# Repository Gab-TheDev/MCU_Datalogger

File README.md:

# MCU_Datalogger
**PCB design of an MCU datalogger**

This project is based on the Data Logger design from KiCad Like a Pro. It involves creating a printed circuit board (PCB) for a microcontroller-based system that records environmental data. The main goal is to design, simulate, and lay out a functional PCB using KiCad, while learning key concepts in schematic capture, component placement, routing, and generating manufacturing files.

The data logger includes a microcontroller, voltage regulation, sensor interfaces (like temperature or humidity sensors), and a method for storing or transmitting data, such as an SD card or serial output. The focus is on building a solid foundation in PCB design practices, including signal integrity, component footprints, and creating a professional-quality layout.

By completing this project, I aim to:
- Gain hands-on experience with KiCad’s schematic and PCB layout tools
- Understand the full workflow from schematic to fabrication
- Apply real-world design constraints (power supply, connectors, etc.)
- Build confidence in creating and testing custom electronics

**COMPONENT DESCRIPTION – ATmega328P based Data Logger**

**ATmega328P-A**<br>
Role: Main microcontroller unit (MCU).<br>
Function: Handles all logic and processing for the data logger. Responsible for reading sensors, managing storage (EEPROM), communicating with the RTC, and executing firmware routines.<br>
Interfaces: Supports I2C, UART, ISCP for embedded systems and data logging.<br>
Clock Input: Works with external crystals (16MHz) for stable timing.<br>

**DS1337S – Real-Time Clock (RTC) – SOIC-8**<br>
Role: Timekeeping chip for timestamping logged data.<br>
Function: Maintains calendar and clock time in the absence of MCU power. Communicates with the MCU over I2C.<br>
Features:
- Battery backup support (via V_BAT)
- 2x programmable square-wave/alarm outputs
- ±2ppm accuracy (with proper crystal)
- Package: SOIC-8 (SOIC127P600X175-8N)

**Battery Connector – PinHeader_1x02_P2.54mm_Vertical**<br>
Role: Backup power source connection for the RTC.<br>
Function: Connects a coin cell battery (e.g., CR2032) to the DS1337’s V_BAT pin to keep time when the main power is off.<br>
Package: Standard 2.54mm pitch, vertical pin header — allows easy external battery hookup or socket.<br>

**32.768 kHz Crystal – SMD_5032 (2-Pin)**<br>
Role: Real-Time Clock (RTC) timebase.<br>
Function: Provides a low-frequency clock source for the DS1337 RTC module to maintain accurate timekeeping with minimal power consumption.<br>
Typical Use: Used for generating 1-second ticks or sub-second timing in RTC chips.<br>
Package: SMD 5.0 x 3.2 mm, hand-solderable.<br>

**32.768 kHz Crystal – SMD_5032 (2-Pin)**<br>
Role: Real-Time Clock (RTC) timebase.<br>
Function: Provides a low-frequency clock source for the DS1337 RTC module to maintain accurate timekeeping with minimal power consumption.<br>
Typical Use: Used for generating 1-second ticks or sub-second timing in RTC chips.<br>
Package: SMD 5.0 x 3.2 mm, hand-solderable footprint.<br>

**24LC1025 – 128 Kbits I²C EEPROM (SOIC-8 Package)**<br>
Role: Non-volatile EEPROM used for persistent data storage in embedded systems. It ensures data retention even when powered off, making it ideal for data logging, configuration storage, and device identification.<br>
Function: It communicates via the I2C protocol and provides 128 Kbits of storage. Data can be written and read by the microcontroller, with the memory content preserved during power loss.<br>
Package: SOIC-8 5.3 x 5.3 mm with a pin pitch of 1.27 mm<br>

**CONCLUSION:**<br>
The MCU Data Logger project is a complete end-to-end solution for building an embedded system that can collect, process, and store data for later analysis. By utilizing KiCad for designing the schematic and PCB, this project serves as both a practical tool and a learning experience for those interested in embedded systems, sensor interfacing, and PCB design.

This repository aims to serve as a valuable resource for developers and hobbyists looking to create reliable and efficient data logging systems, contributing to the growing community of open-source embedded system designs.

## License
This project is licensed under the MIT License - see the LICENSE file for details

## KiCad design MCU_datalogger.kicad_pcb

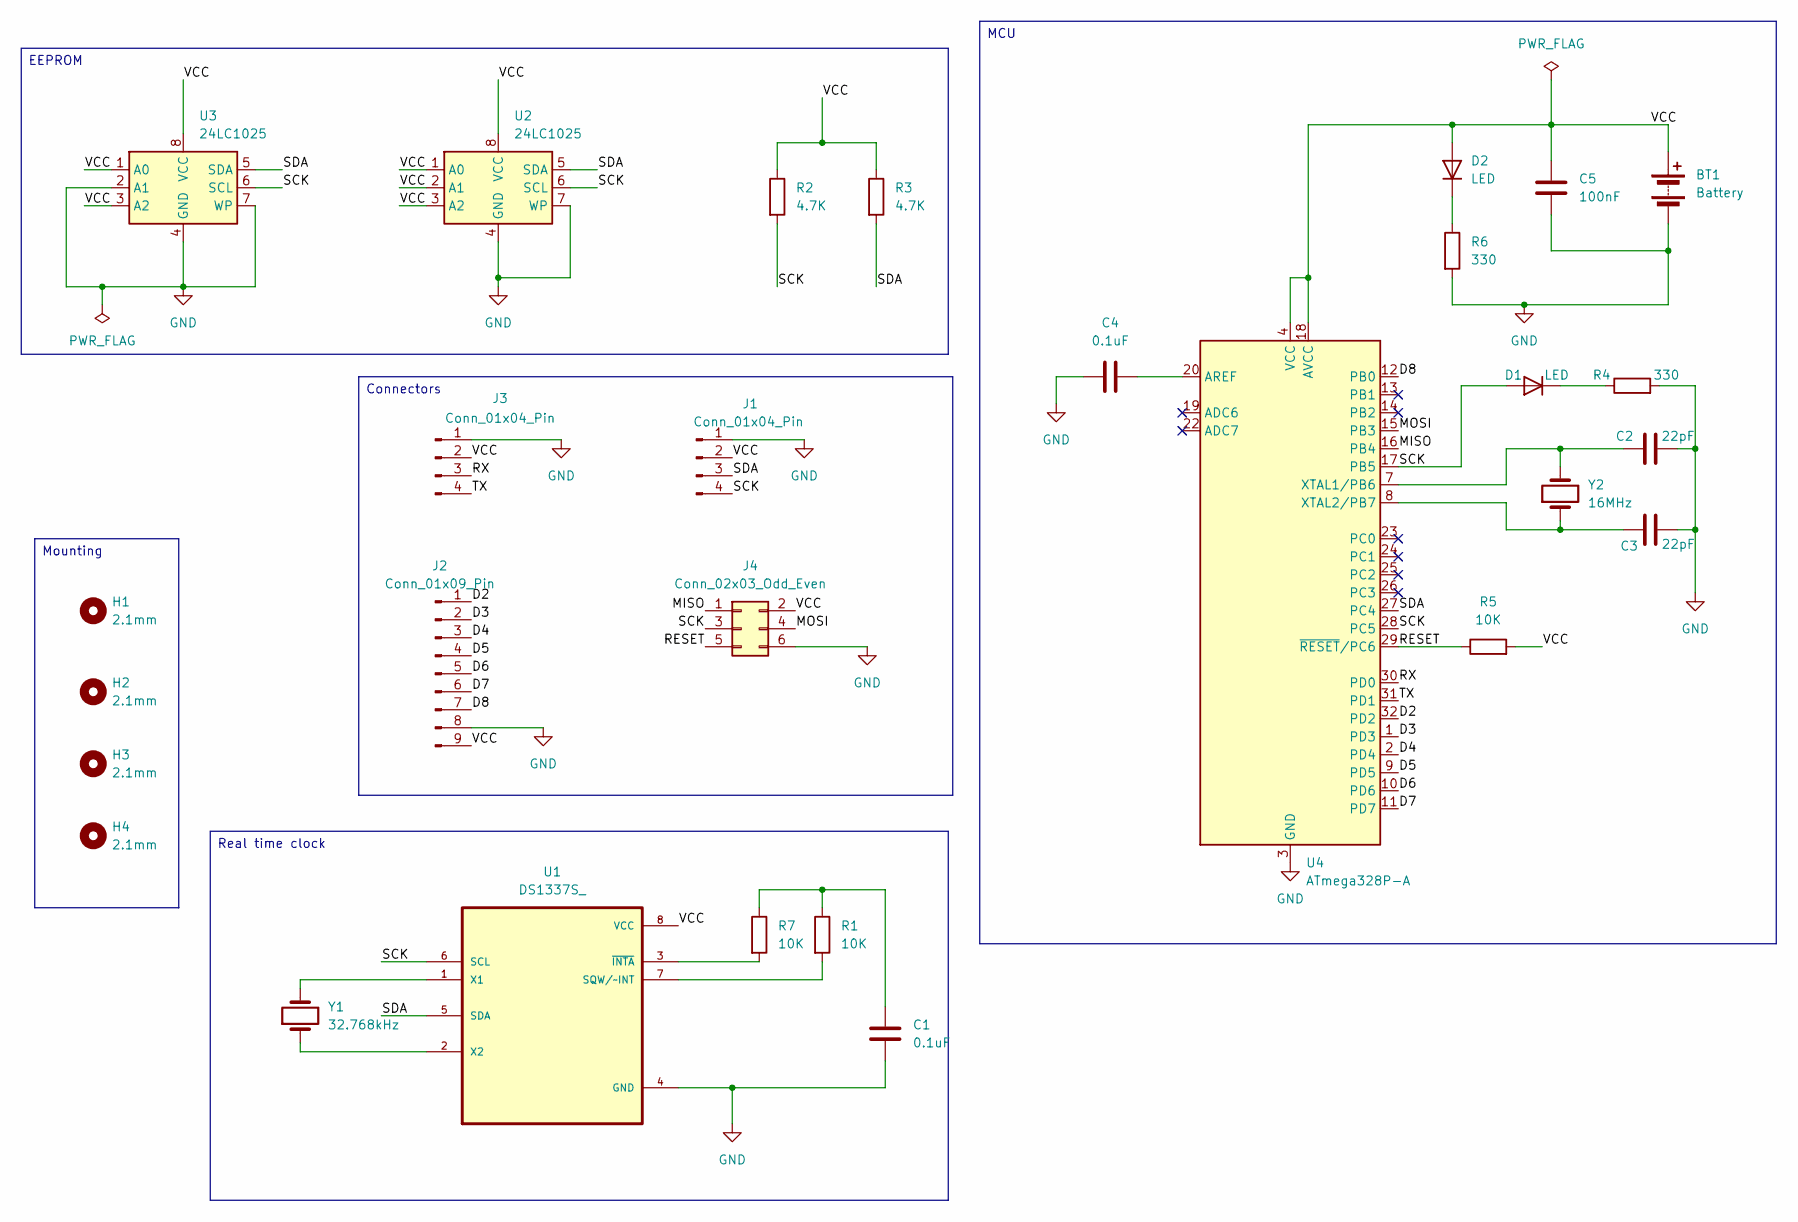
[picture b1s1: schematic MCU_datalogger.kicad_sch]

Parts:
BT1: Battery; PinHeader_1x02_P2.54mm_Vertical
C1, C4: 0.1uF; C_0805_2012Metric
C2, C3: 22pF; C_0805_2012Metric
C5: 100nF; C_0805_2012Metric
D1, D2: LED; LED_0805_2012Metric
H1, H2, H3, H4: 2.1mm; MountingHole_2.1mm
J1, J3: Conn_01x04_Pin; PinHeader_1x04_P2.54mm_Vertical
J2: Conn_01x09_Pin; PinHeader_1x09_P2.54mm_Vertical
J4: Conn_02x03_Odd_Even; PinHeader_2x03_P2.54mm_Vertical
R1, R5, R7: 10K; R_0805_2012Metric
R2, R3: 4.7K; R_0805_2012Metric
R4, R6: 330; R_0805_2012Metric
U1: DS1337S_; SOIC127P600X175-8N
U2, U3: 24LC1025; SOIC-8_5.3x5.3mm_P1.27mm
U4: ATmega328P-A; TQFP-32_7x7mm_P0.8mm
Y1: 32.768kHz; Crystal_SMD_5032-2Pin_5.0x3.2mm_HandSoldering
Y2: 16MHz; Crystal_SMD_5032-2Pin_5.0x3.2mm_HandSoldering

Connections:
/D2: J2.1, U4.32 (PD2)
/D3: J2.2, U4.1 (PD3)
/D4: J2.3, U4.2 (PD4)
/D5: J2.4, U4.9 (PD5)
/D6: J2.5, U4.10 (PD6)
/D7: J2.6, U4.11 (PD7)
/D8: J2.7, U4.12 (PB0)
/MISO: J4.1, U4.16 (PB4)
/MOSI: J4.4, U4.15 (PB3)
/RESET: J4.5, R5.1, U4.29 (~RESET/PC6)
/RX: J3.3, U4.30 (PD0)
/SCK: D1.2 (A), J1.4, J4.3, R2.2, U1.6 (SCL), U2.6 (SCL), U3.6 (SCL), U4.17 (PB5), U4.28 (PC5)
/SDA: J1.3, R3.2, U1.5 (SDA), U2.5 (SDA), U3.5 (SDA), U4.27 (PC4)
/TX: J3.4, U4.31 (PD1)
/VCC: BT1.1 (+), C5.1, D2.2 (A), J1.2, J2.9, J3.2, J4.2, R2.1, R3.1, R5.2, U1.8 (VCC), U2.1 (A0), U2.2 (A1), U2.3 (A2), U2.8 (VCC), U3.1 (A0), U3.3 (A2), U3.8 (VCC), U4.4 (VCC), U4.6 (VCC), U4.18 (AVCC)
GND: BT1.2 (-), C1.2, C2.2, C3.1, C4.1, C5.2, J1.1, J2.8, J3.1, J4.6, R4.2, R6.2, U1.4 (GND), U2.4 (GND), U2.7 (WP), U3.2 (A1), U3.4 (GND), U3.7 (WP), U4.3 (GND), U4.5 (GND), U4.21 (GND)
unnamed: C1.1, R1.1, R7.1
unnamed: D1.1 (K), R4.1
unnamed: D2.1 (K), R6.1
unnamed: R1.2, U1.7 (SQW/~INT)
unnamed: U1.1 (X1), Y1.2
unnamed: U1.2 (X2), Y1.1
unnamed: R7.2, U1.3 (~INTA)
unnamed: C4.2, U4.20 (AREF)
unnamed: C2.1, U4.7 (XTAL1/PB6), Y2.2
unnamed: C3.2, U4.8 (XTAL2/PB7), Y2.1

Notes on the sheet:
Connectors
EEPROM
Real time clock
Mounting
MCU

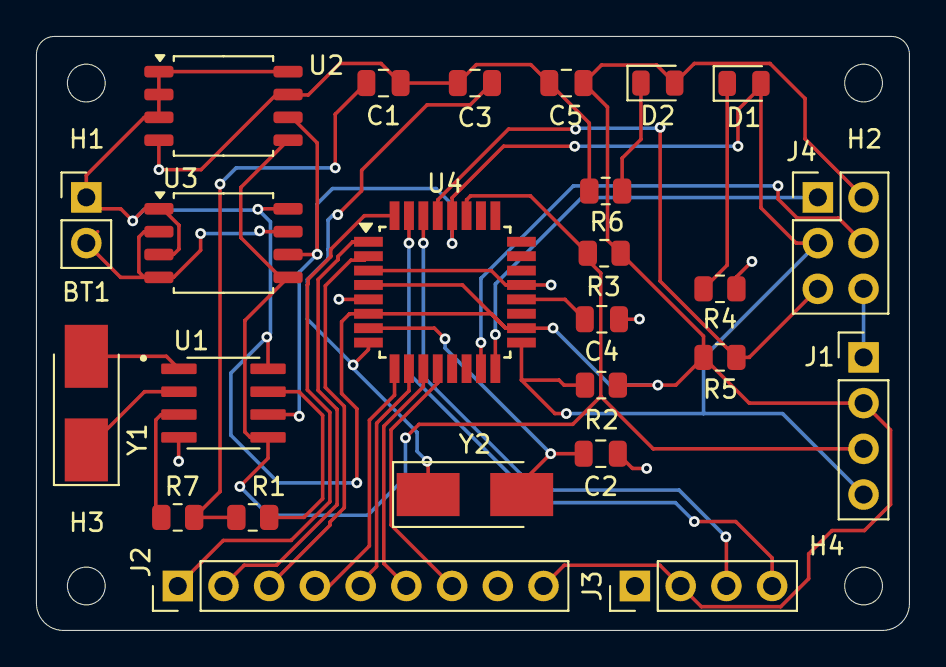
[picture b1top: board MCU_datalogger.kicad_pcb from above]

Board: 2 copper layers, 48.5 x 33.0 mm, 29 parts (0 on the bottom side), 26 nets.

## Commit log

2025-04-10 Create LICENCE
